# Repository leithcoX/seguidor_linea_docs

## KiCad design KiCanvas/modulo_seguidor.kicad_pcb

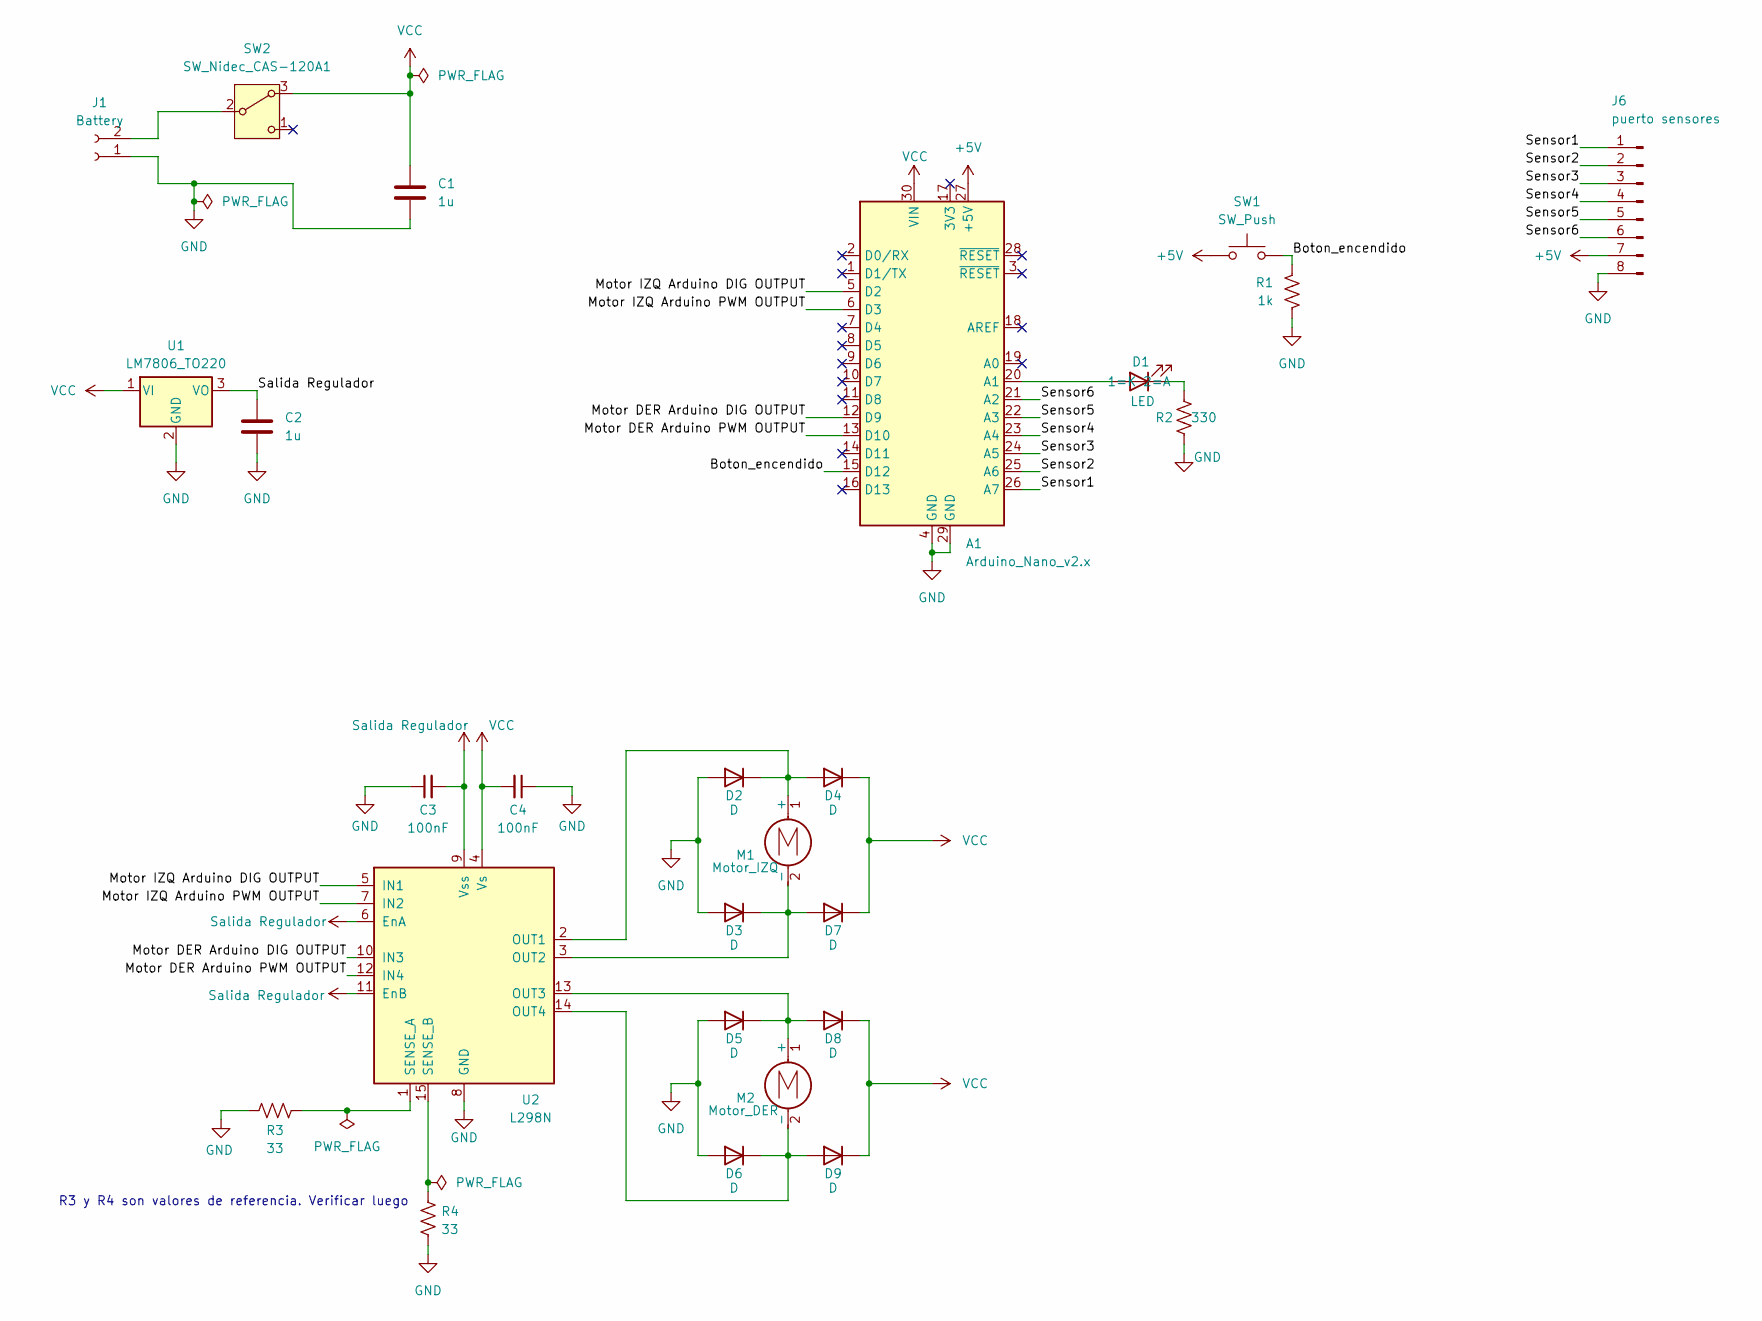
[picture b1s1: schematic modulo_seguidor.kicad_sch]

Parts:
A1: Arduino_Nano_v2.x; Arduino_Nano
C1, C2: 1u; C_1206_3216Metric_Pad1.33x1.80mm_HandSolder
C3, C4: 100nF; C_1206_3216Metric_Pad1.33x1.80mm_HandSolder
D1: LED; LED_D5.0mm
D2, D3, D4, D5, D6, D7, D8, D9: D; D_DO-41_SOD81_P7.62mm_Horizontal
J1: Battery; Molex_KK-254_AE-6410-02A_1x02_P2.54mm_Vertical
J6: puerto sensores; PinHeader_1x08_P2.54mm_Vertical
M1: Motor_IZQ; Molex_KK-254_AE-6410-02A_1x02_P2.54mm_Vertical
M2: Motor_DER; Molex_KK-254_AE-6410-02A_1x02_P2.54mm_Vertical
R1: 1k; R_1206_3216Metric_Pad1.30x1.75mm_HandSolder
R2: 330; R_1206_3216Metric_Pad1.30x1.75mm_HandSolder
R3, R4: 33; R_0805_2012Metric_Pad1.20x1.40mm_HandSolder
SW1: SW_Push; SW_PUSH_6mm
SW2: SW_Nidec_CAS-120A1; Converter_DCDC_TRACO_TSR2-xxxx_THT
U1: LM7806_TO220; TO-220-3_Vertical
U2: L298N; TO-220-15_P2.54x5.08mm_StaggerOdd_Lead4.58mm_Vertical

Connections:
+5V: A1.27 (+5V), J6.7, SW1.1
/Boton_encendido: A1.15 (D12), R1.1, SW1.2
/Motor DER Arduino DIG OUTPUT: A1.12 (D9), U2.10 (IN3)
/Motor DER Arduino PWM OUTPUT: A1.13 (D10), U2.12 (IN4)
/Motor IZQ Arduino DIG OUTPUT: A1.5 (D2), U2.5 (IN1)
/Motor IZQ Arduino PWM OUTPUT: A1.6 (D3), U2.7 (IN2)
/Sensor1: A1.26 (A7), J6.1
/Sensor2: A1.25 (A6), J6.2
/Sensor3: A1.24 (A5), J6.3
/Sensor4: A1.23 (A4), J6.4
/Sensor5: A1.22 (A3), J6.5
/Sensor6: A1.21 (A2), J6.6
GND: A1.4 (GND), A1.29 (GND), C1.2, C2.2, C3.1, C4.1, D2.2 (A), D3.2 (A), D5.2 (A), D6.2 (A), J1.1, J6.8, R1.2, R2.2, R3.2, R4.1, U1.2 (GND), U2.8 (GND)
unnamed: A1.20 (A1), D1.2 (A)
unnamed: D1.1 (K), R2.1
unnamed: D2.1 (K), D4.2 (A), M1.1 (+), U2.2 (OUT1)
unnamed: D3.1 (K), D7.2 (A), M1.2 (-), U2.3 (OUT2)
unnamed: D5.1 (K), D8.2 (A), M2.1 (+), U2.13 (OUT3)
unnamed: D6.1 (K), D9.2 (A), M2.2 (-), U2.14 (OUT4)
unnamed: J1.2, SW2.2 (B)
unnamed: R3.1, U2.1 (SENSE_A)
unnamed: R4.2, U2.15 (SENSE_B)
Salida Regulador: C2.1, C3.2, U1.3 (VO), U2.6 (EnA), U2.9 (Vss), U2.11 (EnB)
VCC: A1.30 (VIN), C1.1, C4.2, D4.1 (K), D7.1 (K), D8.1 (K), D9.1 (K), SW2.3 (A), U1.1 (VI), U2.4 (Vs)

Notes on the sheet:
R3 y R4 son valores de referencia. Verificar luego

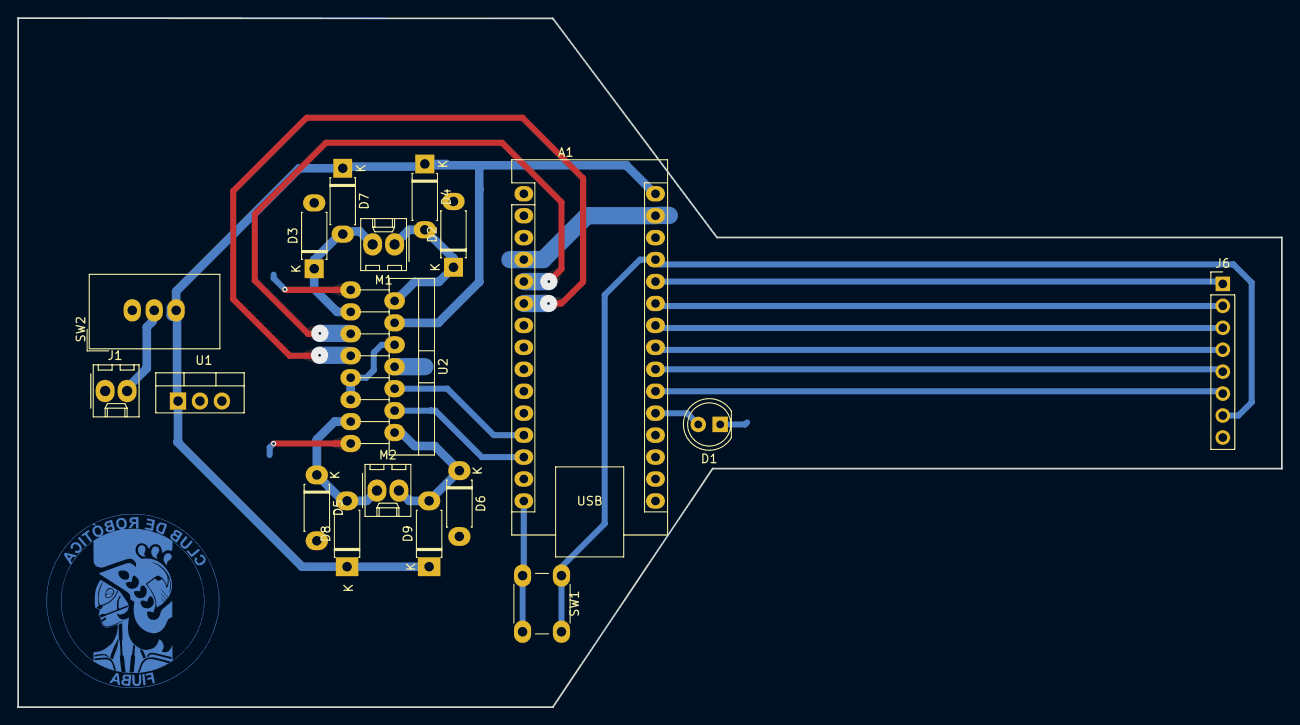
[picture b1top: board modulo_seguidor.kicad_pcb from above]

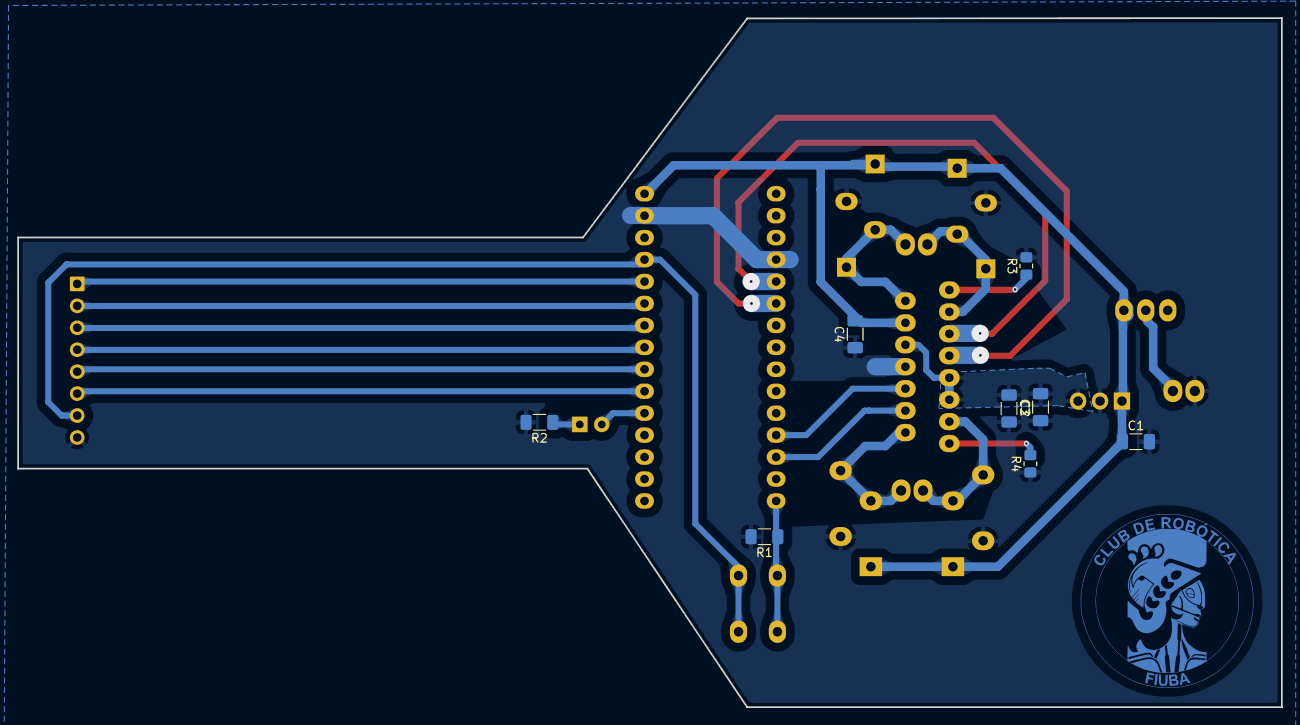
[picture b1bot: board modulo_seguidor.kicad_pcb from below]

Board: 2 copper layers, 146.3 x 79.8 mm, 27 parts (8 on the bottom side), 24 nets.

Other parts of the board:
LOGO: CDR FIUBA; CDR_Logo_20x20.1_Inverted

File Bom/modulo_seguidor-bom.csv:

Row,Description,Part,References,Value,Footprint,Quantity Per PCB,Status,Datasheet,Sim.Device,Sim.Pins
1,Arduino Nano v2.x,Arduino_Nano_v2.x,A1,Arduino_Nano_v2.x,Arduino_Nano,1, ,https://www.arduino.cc/en/uploads/Main/ArduinoNanoManual23.pdf,,
2,"Unpolarized capacitor, small symbol",C_Small,C3 C4,100nF,C_1206_3216Metric_Pad1.33x1.80mm_HandSolder,2, ,~,,
3,Unpolarized capacitor,C,C1 C2,1u,C_1206_3216Metric_Pad1.33x1.80mm_HandSolder,2, ,~,,
4,Diode,D,D2 D3 D4 D5 D6 D7 D8 D9,D,D_DO-41_SOD81_P7.62mm_Horizontal,8, ,~,D,1=K 2=A
5,Light emitting diode,LED,D1,LED,LED_D5.0mm,1, ,~,,1=K 2=A
6,"Generic connector, single row, 01x02, script generated",Conn_01x02_Socket,J1,Battery,Molex_KK-254_AE-6410-02A_1x02_P2.54mm_Vertical,1, ,~,,
7,"Generic connector, single row, 01x08, script generated",Conn_01x08_Pin,J6,puerto sensores,PinHeader_1x08_P2.54mm_Vertical,1, ,~,,
8,DC Motor,Motor_DC,M2,Motor_DER,Molex_KK-254_AE-6410-02A_1x02_P2.54mm_Vertical,1, ,~,,
9,DC Motor,Motor_DC,M1,Motor_IZQ,Molex_KK-254_AE-6410-02A_1x02_P2.54mm_Vertical,1, ,~,,
10,"Resistor, US symbol",R_US,R3 R4,33,R_0805_2012Metric_Pad1.20x1.40mm_HandSolder,2, ,~,,
11,"Resistor, US symbol",R_US,R2,330,R_1206_3216Metric_Pad1.30x1.75mm_HandSolder,1, ,~,,
12,"Resistor, US symbol",R_US,R1,1k,R_1206_3216Metric_Pad1.30x1.75mm_HandSolder,1, ,~,,
13,"Switch, single pole double throw",SW_Nidec_CAS-120A1,SW2,SW_Nidec_CAS-120A1,Converter_DCDC_TRACO_TSR2-xxxx_THT,1, ,https://www.nidec-components.com/e/catalog/switch/cas.pdf,,
14,"Push button switch, generic, two pins",SW_Push,SW1,SW_Push,SW_PUSH_6mm,1, ,~,,
15,"Dual full bridge motor driver, up to 46V, 4A, Multiwatt15-V",L298N,U2,L298N,TO-220-15_P2.54x5.08mm_StaggerOdd_Lead4.58mm_Vertical,1, ,http://www.st.com/st-web-ui/static/active/en/resource/techni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,,
16,"Positive 1A 35V Linear Regulator, Fixed Output 6V, TO-220",LM7806_TO220,U1,LM7806_TO220,TO-220-3_Vertical,1, ,https://www.onsemi.cn/PowerSolutions/document/MC7800-D.PDF,,





Project info:
Schematic:,modulo_seguidor
Variant:,default
Revision:,
Date:,2025-08-31_02-43-57
KiCad Version:,9.0.1+1
Statistics:
Component Groups:,16
Component Count:,26
Fitted Components:,26
Number of PCBs:,1
Total Components:,26

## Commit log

2025-09-09 fix: Move html to root directory
2025-09-09 fix: index.html name
